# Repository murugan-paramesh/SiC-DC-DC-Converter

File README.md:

# SiC isolated DC-DC converters: PSFB 3 kW baseline and 6.6 kW bidirectional DAB research platform

Two complete, script-generated KiCad 7 hardware designs with their calculations, simulations, firmware
and documentation. Nothing here has been built or measured; every result is labelled by how it was
obtained (calculation, simulation, software-in-the-loop, DRC).

| Design | Where | Status |
|---|---|---|
| **PSFB 3 kW**, 400 V -> 48 V, SiC primary, synchronous rectification, UCC28951 | `hardware/kicad/SiC_PSFB_3kW.kicad_pro`, `docs/`, `tools/`, `simulation/` | schematic generated and netlist-verified; 4-layer PCB generated, fully routed, KiCad DRC 0 errors / 0 unconnected (`hardware/kicad/drc_summary.json`); gerbers/drill/pos in `hardware/outputs/`; switched simulation agrees with the design |
| **DAB 6.6 kW**, 650-850 V <-> 300-450 V bidirectional, SiC both bridges, C2000 control | `SiC_6k6_Industrial_DAB/` (see its README) | full research/engineering chain: requirements, models, design, simulation (Python + ngspice), control + firmware (SIL-tested), 6-layer KiCad PCB, thermal/EMI/safety/FMEA, optimisation, BOM, manufacturing outputs, verification report, research report, lab plan |

Shared tooling: `tools/kicad/` (symbol/footprint generators, hierarchical schematic generator,
`boardgen.py` PCB builder on the pcbnew API with a negotiated-congestion grid router and DRC).

Quick start (PSFB): `python3 tools/psfb_design.py && python3 -m tools.kicad.gen_schematic && python3 -m tools.kicad.gen_pcb`.
Quick start (DAB): see `SiC_6k6_Industrial_DAB/README.md`.

2026 research upgrade: `Advanced_Research_2026/` (gap analysis, verified literature database, digital twin,
adaptive MPC, FEM-lite magnetics, parasitic extraction, robust optimisation, UQ, health monitoring, gate drive,
reliability, HIL plan, cybersecurity, benchmarks, publication drafts, maturity matrix - every module states
its maturity level and what it could not verify; nothing is above L3). Beginner-to-expert learning notes with
viva questions and the combined textbook: `21_Human_Friendly_Learning_Notes/`.

Safety: both designs carry hazardous voltages (420 V / 850 V DC). No prototype should be energised
before an independent engineering review and an approved laboratory procedure
(`SiC_6k6_Industrial_DAB/20_Experimental_Test_Plan/`).

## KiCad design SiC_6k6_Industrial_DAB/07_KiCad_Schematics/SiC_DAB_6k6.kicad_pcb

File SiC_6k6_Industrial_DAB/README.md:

# SiC 6.6 kW Industrial Bidirectional DAB - research and engineering package

Bidirectional dual active bridge, 650-850 V DC <-> 300-450 V DC, 6.6 kW, 100 kHz, 1200 V SiC on
both bridges, TI C2000 digital control. Everything in this directory is generated or verified by
scripts; **no hardware has been built, energised or measured**. The PSFB 3 kW design at the
repository root is the preserved baseline (`Legacy_PSFB_Baseline/README.md`).

## Directory map

| Folder | Content | How it was verified |
|---|---|---|
| `00_Requirements/` | existing-project audit, requirements with explicit service conditions, operating-envelope definition, RTM (`03_RTM.csv`) | reviewed; status column refreshed by `18_Verification/run_verification.py` |
| `01_Literature_Review/` | 38 references (DAB, modulation, SiC, magnetics, control, standards) with a citation-policy note | recalled, to cross-check |
| `02_Topology_Comparison/` | `topology_comparison.py` -> quantitative PSFB/DAB/CLLLC/2-ph/3-ph comparison, decision | script run |
| `03_Mathematical_Models/` | derivations (SPS/EPS/DPS/TPS, ZVS, losses, averaged model) ; code in `dabtools/dab/` | numeric vs closed form < 0.1 % |
| `04_Design_Calculations/` | `dab_design.py` -> `design_values.json`, `design_report.md`, derating/ZVS maps, loss budget, DC link, protection thresholds | script run |
| `05_Simulation/` | closed-loop switched model (`run_switched_sim.py`), ngspice switching model (`gen_spice.py`), results + plots | both run; agree with analysis |
| `06_Magnetics/` | transformer/inductor design, core comparison, insulation, test procedure | script run |
| `07_KiCad_Schematics/` | **KiCad 7 project** `SiC_DAB_6k6.kicad_pro` (5 sheets, 261 components) + the 6-layer PCB `SiC_DAB_6k6.kicad_pcb`, libraries, DRC report | netlist export = design database; DRC via pcbnew: **0 errors, 0 unconnected** (run 27, see 08 and 18) |
| `08_KiCad_PCB/` | layout description, run history, board images (the PCB file lives with the project in 07) | DRC 0 errors / 0 unconnected, 63 silkscreen/stub warnings |
| `09_Component_Libraries/` | pointer to `07_KiCad_Schematics/lib/` and the generators | pin-existence check |
| `10_Firmware/` | portable C control core, protocol, C2000 HAL (not compiled), SIL harness (`make test`) | 30 SIL checks pass (gcc) |
| `11_Control_Algorithms/` | loop design, modulation comparison, MPC alternative, `control_params.json` | script run |
| `12_Optimization/` | exhaustive design-space exploration, Pareto front, sensitivities | script run |
| `13_Thermal_Analysis/` | losses -> Tj, cooling options, derating | script run |
| `14_EMI_EMC/` | DM/CM estimate, filter, standards, pre-compliance plan | script run |
| `15_Safety_Reliability/` | insulation coordination (IEC 62477-1/60664-1 basis), protection coordination, FMEA | analysis |
| `16_BOM/` | BOM with ratings/derating, flags for unverified parts, off-board items | generated |
| `17_Manufacturing/` | stack-up, notes, `export_outputs.py` (gerbers, drill, pos, PDFs) | kicad-cli |
| `18_Verification/` | `run_verification.py` -> `verification_report.md` (what ran, what passed) | - |
| `19_Research_Report/` | `build_report.py` -> `report.md` (28 chapters, numbers pulled from result files) | generated |
| `20_Experimental_Test_Plan/` | staged laboratory plan, instruments, criteria, safety controls | procedure only |
| `dabtools/` | Python packages: `dab/` (models), `kicad_dab/` (design database, schematic/PCB/BOM generators) | - |

## Reproduce everything

```
cd SiC_6k6_Industrial_DAB
pip install numpy matplotlib            # KiCad 7 (kicad-cli + pcbnew python), ngspice, gcc required
python3 02_Topology_Comparison/topology_comparison.py
python3 04_Design_Calculations/dab_design.py
python3 06_Magnetics/transformer_design.py
python3 05_Simulation/run_switched_sim.py && python3 05_Simulation/gen_spice.py
python3 11_Control_Algorithms/control_design.py
python3 12_Optimization/optimize.py
python3 13_Thermal_Analysis/thermal_analysis.py && python3 14_EMI_EMC/emi_analysis.py
(cd 10_Firmware && python3 tools/gen_params.py && make test)
python3 dabtools/kicad_dab/gen_sch_dab.py        # schematic + libraries + netlist check
python3 dabtools/kicad_dab/gen_pcb_dab.py        # placement, planes, routing, zone fill, DRC (long)
python3 dabtools/kicad_dab/bom_dab.py
python3 17_Manufacturing/export_outputs.py
python3 18_Verification/run_verification.py
python3 19_Research_Report/build_report.py
```

## Completion matrix

See `18_Verification/verification_report.md` for the current tool results and
`00_Requirements/03_RTM.csv` for the per-requirement status. Summary of the states used:
*completed* (artefact exists and its generator ran), *generated but not verified* (C2000 HAL,
BoosterPack mapping, bias-module choice), *simulation-validated* (control, power stage),
*engineering-reviewed* (none yet - independent review required), *experimentally validated*
(none), *blocked* (push to GitHub pending repository access), *remaining work* (chapter 23 of
the report).

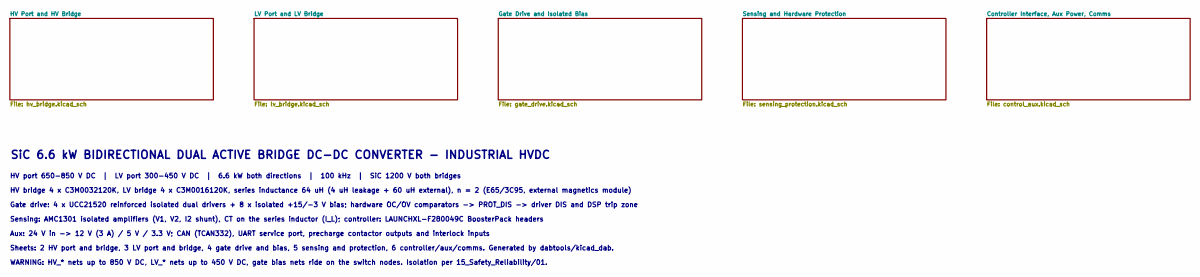
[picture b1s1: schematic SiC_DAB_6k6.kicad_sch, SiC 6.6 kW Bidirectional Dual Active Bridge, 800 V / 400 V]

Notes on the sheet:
SiC 6.6 kW BIDIRECTIONAL DUAL ACTIVE BRIDGE DC-DC CONVERTER - INDUSTRIAL HVDC
HV port 650-850 V DC | LV port 300-450 V DC | 6.6 kW both directions | 100 kHz | SiC 1200 V both bridges
HV bridge 4 x C3M0032120K, LV bridge 4 x C3M0016120K, series inductance 64 uH (4 uH leakage + 60 uH external), n = 2 (E65/3C95, external magnetics module)
Gate drive: 4 x UCC21520 reinforced isolated dual drivers + 8 x isolated +15/-3 V bias; hardware OC/OV comparators -> PROT_DIS -> driver DIS and DSP trip zone
Sensing: AMC1301 isolated amplifiers (V1, V2, I2 shunt), CT on the series inductor (I_L); controller: LAUNCHXL-F280049C BoosterPack headers
Aux: 24 V in -> 12 V (3 A) / 5 V / 3.3 V; CAN (TCAN332), UART service port, precharge contactor outputs and interlock inputs
Sheets: 2 HV port and bridge, 3 LV port and bridge, 4 gate drive and bias, 5 sensing and protection, 6 controller/aux/comms. Generated by dabtools/kicad_dab.
WARNING: HV_* nets up to 850 V DC, LV_* nets up to 450 V DC, gate bias nets ride on the switch nodes. Isolation per 15_Safety_Reliability/01.

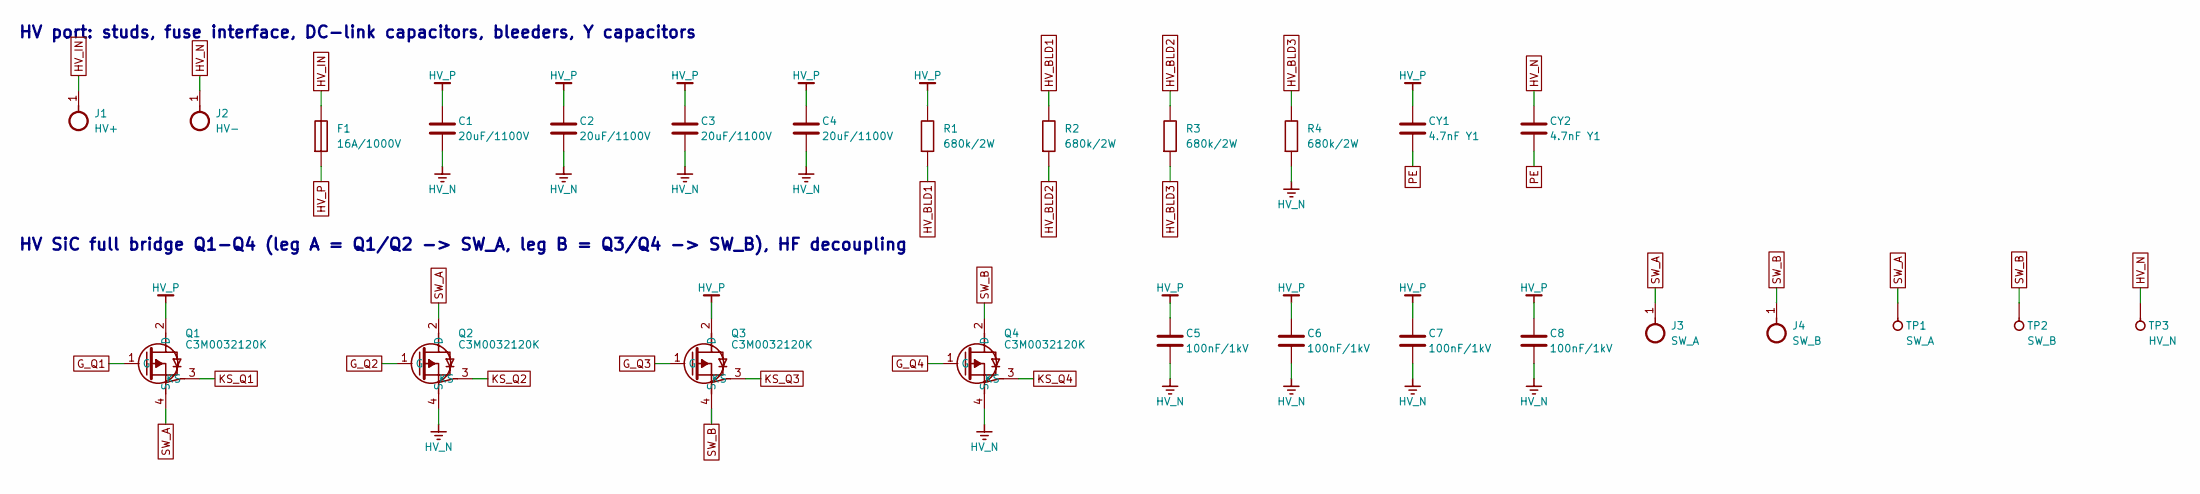
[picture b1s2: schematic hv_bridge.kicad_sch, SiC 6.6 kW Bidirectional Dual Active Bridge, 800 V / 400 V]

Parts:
C1, C2, C3, C4: 20uF/1100V; C_Film_P52.5; MPN TDK B32778J0206K (verify 1100 V variant)
C5, C6, C7, C8: 100nF/1kV; C_2220; MPN TDK CGA9N4X7T2W104K (verify)
CY1, CY2: 4.7nF Y1; C_Y1_P12.5; MPN Vishay VY1472M63Y5UQ63V0
F1: 16A/1000V; Fuse_Terminal_M6; MPN Bussmann FWP-16A14F class (verify)
J1: HV+; Stud_M6
J2: HV-; Stud_M6
J3: SW_A; Stud_M6
J4: SW_B; Stud_M6
Q1, Q2, Q3, Q4: C3M0032120K; TO-247-4_Vertical; MPN Wolfspeed C3M0032120K
R1, R2, R3, R4: 680k/2W; R_2512
TP1: SW_A; TestPoint
TP2: SW_B; TestPoint
TP3: HV_N; TestPoint

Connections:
G_Q1: Q1.1 (G); also elsewhere on the board
G_Q2: Q2.1 (G); also elsewhere on the board
G_Q3: Q3.1 (G); also elsewhere on the board
G_Q4: Q4.1 (G); also elsewhere on the board
HV_BLD1: R1.2, R2.1
HV_BLD2: R2.2, R3.1
HV_BLD3: R3.2, R4.1
HV_IN: F1.1, J1.1
HV_N: C1.2, C2.2, C3.2, C4.2, C5.2, C6.2, C7.2, C8.2, CY2.1, J2.1, Q2.4 (S), Q4.4 (S), R4.2, TP3.1; also elsewhere on the board
HV_P: C1.1, C2.1, C3.1, C4.1, C5.1, C6.1, C7.1, C8.1, CY1.1, F1.2, Q1.2 (D), Q3.2 (D), R1.1; also elsewhere on the board
KS_Q1: Q1.3 (KS); also elsewhere on the board
KS_Q2: Q2.3 (KS); also elsewhere on the board
KS_Q3: Q3.3 (KS); also elsewhere on the board
KS_Q4: Q4.3 (KS); also elsewhere on the board
PE_HV: CY1.2, CY2.2; also elsewhere on the board
SW_A: J3.1, Q1.4 (S), Q2.2 (D), TP1.1; also elsewhere on the board
SW_B: J4.1, Q3.4 (S), Q4.2 (D), TP2.1

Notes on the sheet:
HV port: studs, fuse interface, DC-link capacitors, bleeders, Y capacitors
HV SiC full bridge Q1-Q4 (leg A = Q1/Q2 -> SW_A, leg B = Q3/Q4 -> SW_B), HF decoupling

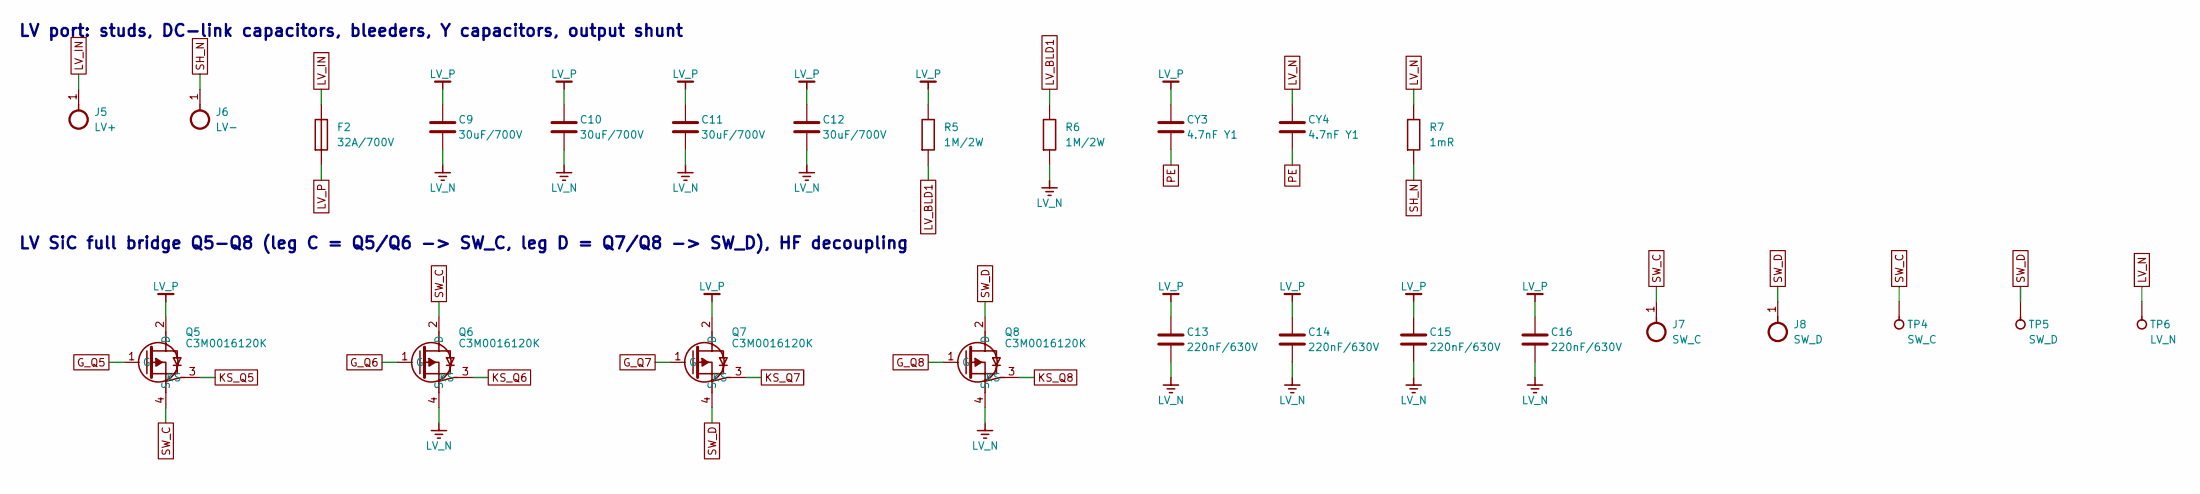
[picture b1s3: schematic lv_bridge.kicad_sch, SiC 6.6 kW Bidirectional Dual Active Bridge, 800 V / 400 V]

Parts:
C9, C10, C11, C12: 30uF/700V; C_Film_P37.5; MPN TDK B32778G7306K (verify)
C13, C14, C15, C16: 220nF/630V; C_2220; MPN TDK CGA9P4X7T2J224K (verify)
CY3, CY4: 4.7nF Y1; C_Y1_P12.5; MPN Vishay VY1472M63Y5UQ63V0
F2: 32A/700V; Fuse_Terminal_M6; MPN Bussmann FWP-32A14F class (verify)
J5: LV+; Stud_M6
J6: LV-; Stud_M6
J7: SW_C; Stud_M6
J8: SW_D; Stud_M6
Q5, Q6, Q7, Q8: C3M0016120K; TO-247-4_Vertical; MPN Wolfspeed C3M0016120K
R5, R6: 1M/2W; R_2512
R7: 1mR; R_Shunt_8518; MPN Vishay WSBS8518L1000JK
TP4: SW_C; TestPoint
TP5: SW_D; TestPoint
TP6: LV_N; TestPoint

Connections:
G_Q5: Q5.1 (G); also elsewhere on the board
G_Q6: Q6.1 (G); also elsewhere on the board
G_Q7: Q7.1 (G); also elsewhere on the board
G_Q8: Q8.1 (G); also elsewhere on the board
KS_Q5: Q5.3 (KS); also elsewhere on the board
KS_Q6: Q6.3 (KS); also elsewhere on the board
KS_Q7: Q7.3 (KS); also elsewhere on the board
KS_Q8: Q8.3 (KS); also elsewhere on the board
LV_BLD1: R5.2, R6.1
LV_IN: F2.1, J5.1
LV_N: C9.2, C10.2, C11.2, C12.2, C13.2, C14.2, C15.2, C16.2, CY4.1, Q6.4 (S), Q8.4 (S), R6.2, R7.1, TP6.1; also elsewhere on the board
LV_P: C9.1, C10.1, C11.1, C12.1, C13.1, C14.1, C15.1, C16.1, CY3.1, F2.2, Q5.2 (D), Q7.2 (D), R5.1; also elsewhere on the board
PE_LV: CY3.2, CY4.2; also elsewhere on the board
SH_N: J6.1, R7.2; also elsewhere on the board
SW_C: J7.1, Q5.4 (S), Q6.2 (D), TP4.1
SW_D: J8.1, Q7.4 (S), Q8.2 (D), TP5.1

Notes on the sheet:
LV port: studs, DC-link capacitors, bleeders, Y capacitors, output shunt
LV SiC full bridge Q5-Q8 (leg C = Q5/Q6 -> SW_C, leg D = Q7/Q8 -> SW_D), HF decoupling

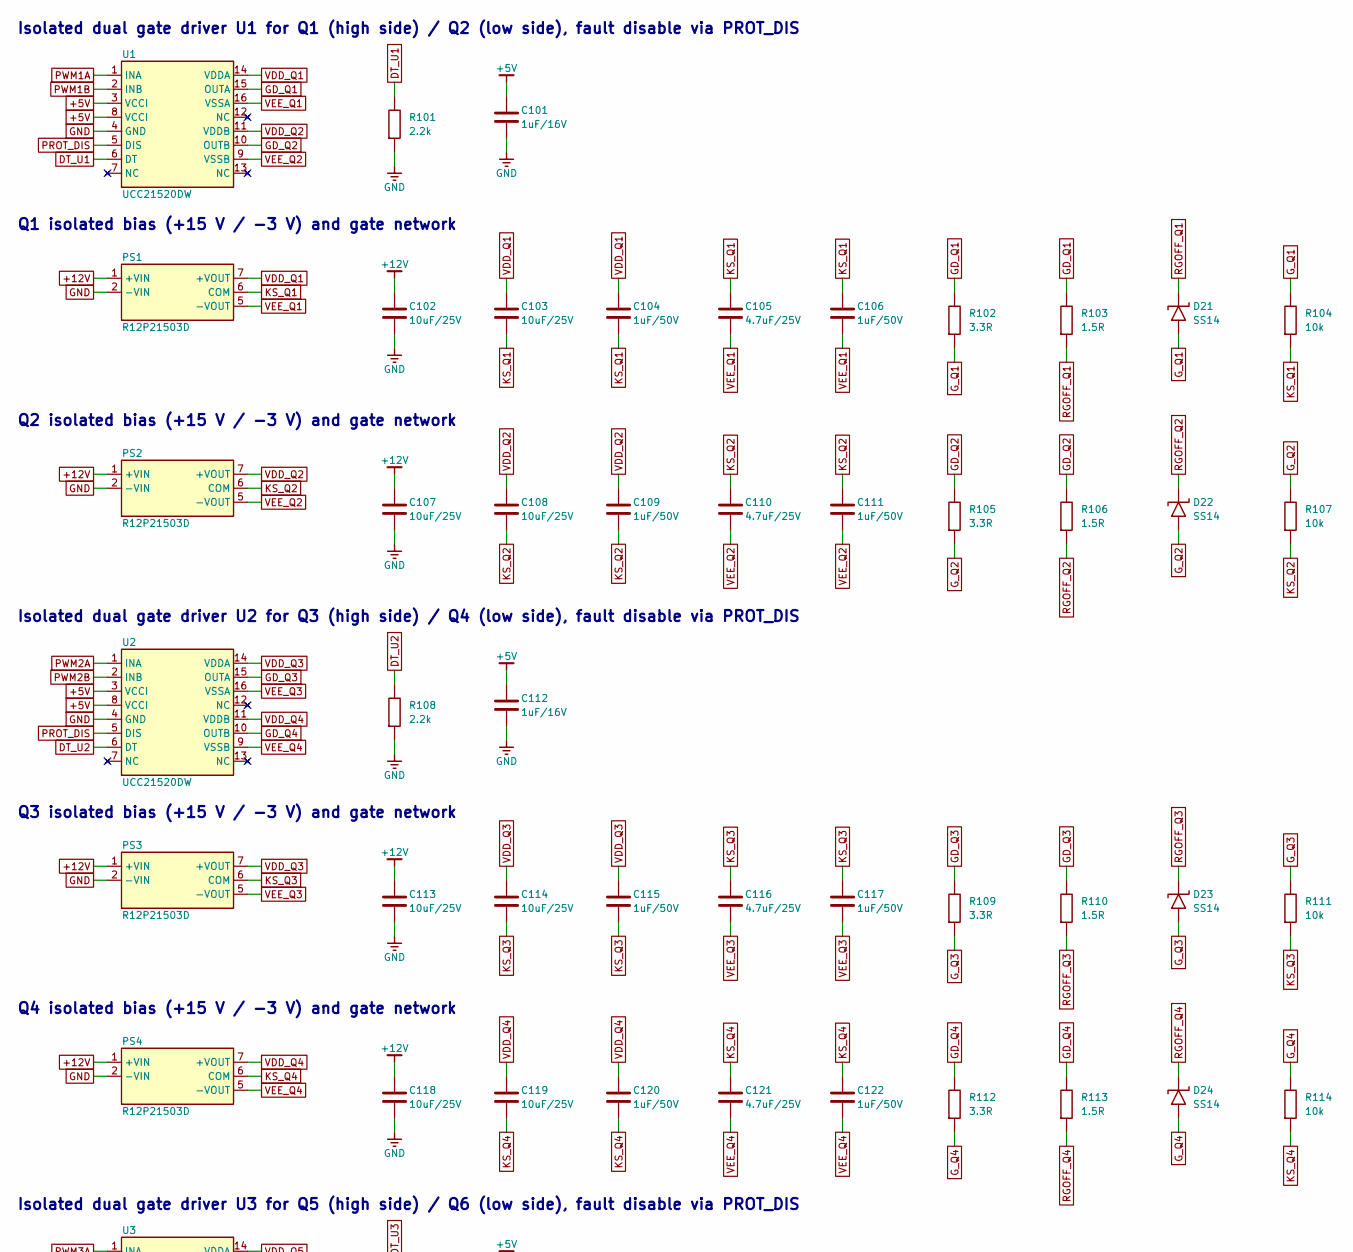
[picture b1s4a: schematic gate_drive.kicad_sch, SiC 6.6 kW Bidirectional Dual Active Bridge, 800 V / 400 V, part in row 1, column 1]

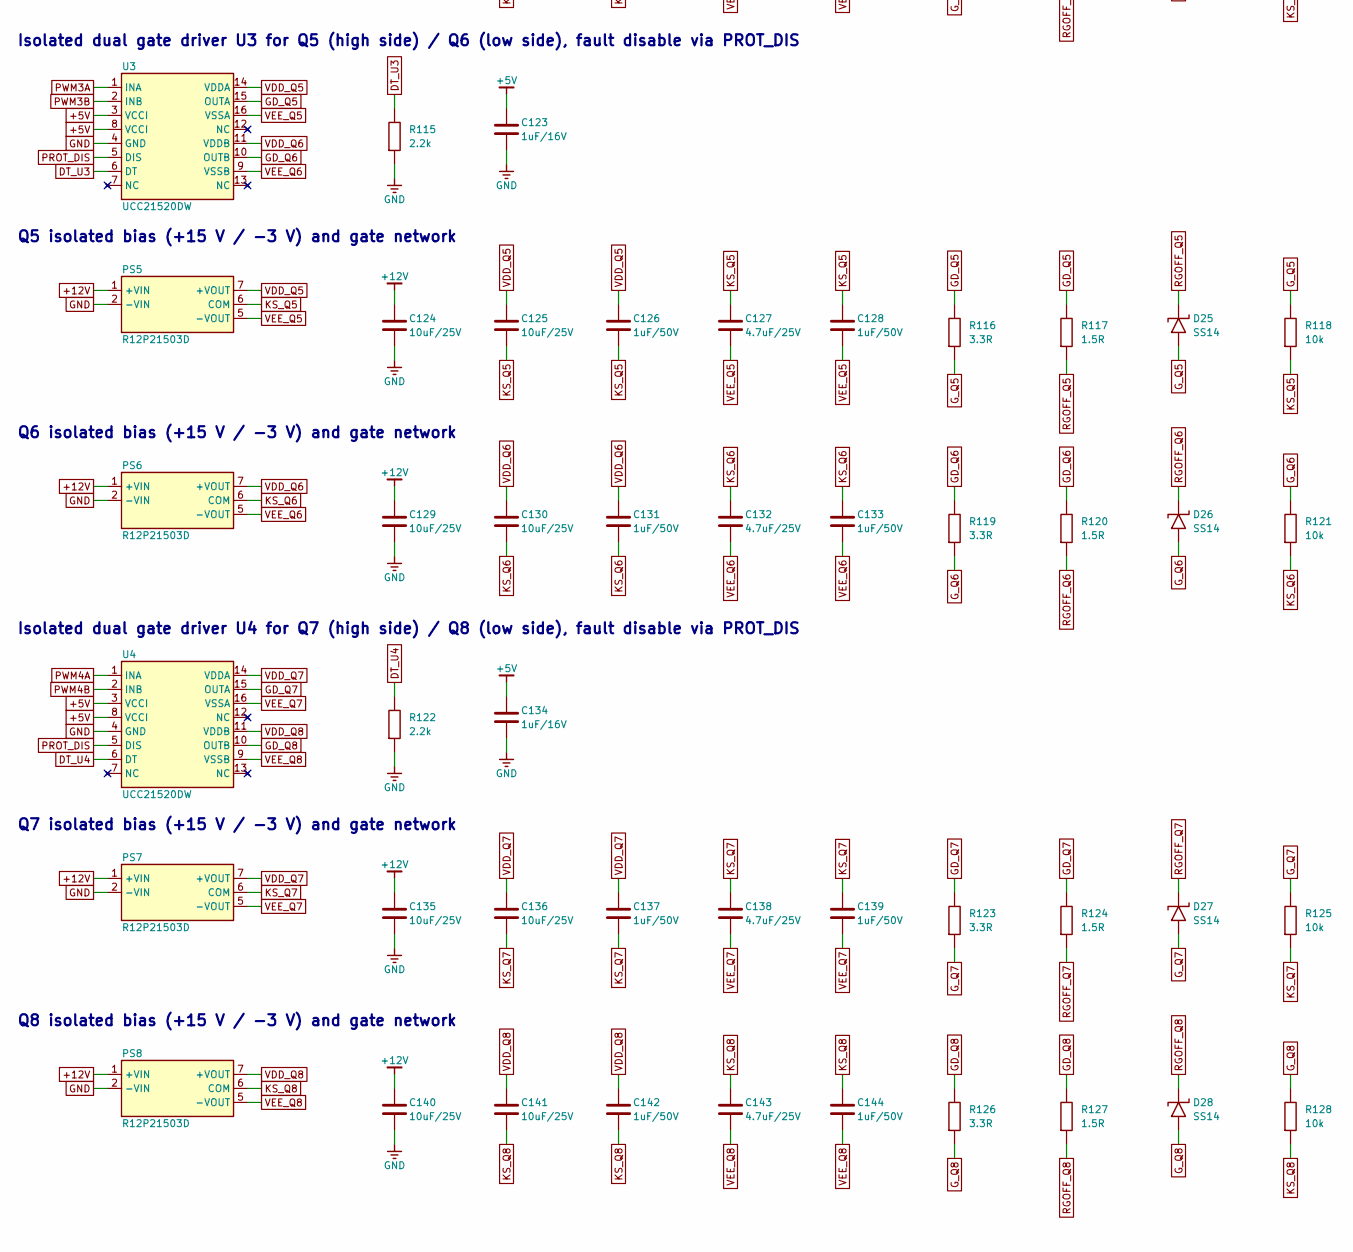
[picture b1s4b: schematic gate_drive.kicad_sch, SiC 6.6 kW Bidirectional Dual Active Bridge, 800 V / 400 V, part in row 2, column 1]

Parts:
C101, C112, C123, C134: 1uF/16V; C_0603
C102, C103, C107, C108, C113, C114, C118, C119, C124, C125, C129, C130, C135, C136, C140, C141: 10uF/25V; C_1206
C104, C106, C109, C111, C115, C117, C120, C122, C126, C128, C131, C133, C137, C139, C142, C144: 1uF/50V; C_0603
C105, C110, C116, C121, C127, C132, C138, C143: 4.7uF/25V; C_0805
D21, D22, D23, D24, D25, D26, D27, D28: SS14; D_SMA; MPN Vishay SS14
PS1, PS2, PS3, PS4, PS5, PS6, PS7, PS8: R12P21503D; SIP-7_IsoDCDC; MPN RECOM R12P21503D (basic-class isolation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
R101, R108, R115, R122: 2.2k; R_0603
R102, R105, R109, R112, R116, R119, R123, R126: 3.3R; R_1206
R103, R106, R110, R113, R117, R120, R124, R127: 1.5R; R_1206
R104, R107, R111, R114, R118, R121, R125, R128: 10k; R_0603
U1, U2, U3, U4: UCC21520DW; SOIC-16W; MPN TI UCC21520DW

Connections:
+5V: C101.1, C112.1, C123.1, C134.1, U1.3 (VCCI), U1.8 (VCCI), U2.3 (VCCI), U2.8 (VCCI), U3.3 (VCCI), U3.8 (VCCI), U4.3 (VCCI), U4.8 (VCCI); also elsewhere on the board
+12V: C102.1, C107.1, C113.1, C118.1, C124.1, C129.1, C135.1, C140.1, PS1.1 (+VIN), PS2.1 (+VIN), PS3.1 (+VIN), PS4.1 (+VIN), PS5.1 (+VIN), PS6.1 (+VIN), PS7.1 (+VIN), PS8.1 (+VIN); also elsewhere on the board
DT_U1: R101.1, U1.6 (DT)
DT_U2: R108.1, U2.6 (DT)
DT_U3: R115.1, U3.6 (DT)
DT_U4: R122.1, U4.6 (DT)
GD_Q1: R102.1, R103.1, U1.15 (OUTA)
GD_Q2: R105.1, R106.1, U1.10 (OUTB)
GD_Q3: R109.1, R110.1, U2.15 (OUTA)
GD_Q4: R112.1, R113.1, U2.10 (OUTB)
GD_Q5: R116.1, R117.1, U3.15 (OUTA)
GD_Q6: R119.1, R120.1, U3.10 (OUTB)
GD_Q7: R123.1, R124.1, U4.15 (OUTA)
GD_Q8: R126.1, R127.1, U4.10 (OUTB)
GND: C101.2, C102.2, C107.2, C112.2, C113.2, C118.2, C123.2, C124.2, C129.2, C134.2, C135.2, C140.2, PS1.2 (-VIN), PS2.2 (-VIN), PS3.2 (-VIN), PS4.2 (-VIN), PS5.2 (-VIN), PS6.2 (-VIN), PS7.2 (-VIN), PS8.2 (-VIN), R101.2, R108.2, R115.2, R122.2, U1.4 (GND), U2.4 (GND), U3.4 (GND), U4.4 (GND); also elsewhere on the board
G_Q1: D21.2 (A), R102.2, R104.1; also elsewhere on the board
G_Q2: D22.2 (A), R105.2, R107.1; also elsewhere on the board
G_Q3: D23.2 (A), R109.2, R111.1; also elsewhere on the board
G_Q4: D24.2 (A), R112.2, R114.1; also elsewhere on the board
G_Q5: D25.2 (A), R116.2, R118.1; also elsewhere on the board
G_Q6: D26.2 (A), R119.2, R121.1; also elsewhere on the board
G_Q7: D27.2 (A), R123.2, R125.1; also elsewhere on the board
G_Q8: D28.2 (A), R126.2, R128.1; also elsewhere on the board
KS_Q1: C103.2, C104.2, C105.1, C106.1, PS1.6 (COM), R104.2; also elsewhere on the board
KS_Q2: C108.2, C109.2, C110.1, C111.1, PS2.6 (COM), R107.2; also elsewhere on the board
KS_Q3: C114.2, C115.2, C116.1, C117.1, PS3.6 (COM), R111.2; also elsewhere on the board
KS_Q4: C119.2, C120.2, C121.1, C122.1, PS4.6 (COM), R114.2; also elsewhere on the board
KS_Q5: C125.2, C126.2, C127.1, C128.1, PS5.6 (COM), R118.2; also elsewhere on the board
KS_Q6: C130.2, C131.2, C132.1, C133.1, PS6.6 (COM), R121.2; also elsewhere on the board
KS_Q7: C136.2, C137.2, C138.1, C139.1, PS7.6 (COM), R125.2; also elsewhere on the board
KS_Q8: C141.2, C142.2, C143.1, C144.1, PS8.6 (COM), R128.2; also elsewhere on the board
PROT_DIS: U1.5 (DIS), U2.5 (DIS), U3.5 (DIS), U4.5 (DIS); also elsewhere on the board
PWM1A: U1.1 (INA); also elsewhere on the board
PWM1B: U1.2 (INB); also elsewhere on the board
PWM2A: U2.1 (INA); also elsewhere on the board
PWM2B: U2.2 (INB); also elsewhere on the board
PWM3A: U3.1 (INA); also elsewhere on the board
PWM3B: U3.2 (INB); also elsewhere on the board
PWM4A: U4.1 (INA); also elsewhere on the board
PWM4B: U4.2 (INB); also elsewhere on the board
RGOFF_Q1: D21.1 (K), R103.2
RGOFF_Q2: D22.1 (K), R106.2
RGOFF_Q3: D23.1 (K), R110.2
RGOFF_Q4: D24.1 (K), R113.2
RGOFF_Q5: D25.1 (K), R117.2
RGOFF_Q6: D26.1 (K), R120.2
RGOFF_Q7: D27.1 (K), R124.2
RGOFF_Q8: D28.1 (K), R127.2
VDD_Q1: C103.1, C104.1, PS1.7 (+VOUT), U1.14 (VDDA)
VDD_Q2: C108.1, C109.1, PS2.7 (+VOUT), U1.11 (VDDB)
VDD_Q3: C114.1, C115.1, PS3.7 (+VOUT), U2.14 (VDDA)
VDD_Q4: C119.1, C120.1, PS4.7 (+VOUT), U2.11 (VDDB)
VDD_Q5: C125.1, C126.1, PS5.7 (+VOUT), U3.14 (VDDA)
VDD_Q6: C130.1, C131.1, PS6.7 (+VOUT), U3.11 (VDDB)
VDD_Q7: C136.1, C137.1, PS7.7 (+VOUT), U4.14 (VDDA)
VDD_Q8: C141.1, C142.1, PS8.7 (+VOUT), U4.11 (VDDB)
VEE_Q1: C105.2, C106.2, PS1.5 (-VOUT), U1.16 (VSSA)
VEE_Q2: C110.2, C111.2, PS2.5 (-VOUT), U1.9 (VSSB)
VEE_Q3: C116.2, C117.2, PS3.5 (-VOUT), U2.16 (VSSA)
VEE_Q4: C121.2, C122.2, PS4.5 (-VOUT), U2.9 (VSSB)
VEE_Q5: C127.2, C128.2, PS5.5 (-VOUT), U3.16 (VSSA)
VEE_Q6: C132.2, C133.2, PS6.5 (-VOUT), U3.9 (VSSB)
VEE_Q7: C138.2, C139.2, PS7.5 (-VOUT), U4.16 (VSSA)
VEE_Q8: C143.2, C144.2, PS8.5 (-VOUT), U4.9 (VSSB)

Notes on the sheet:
Isolated dual gate driver U1 for Q1 (high side) / Q2 (low side), fault disable via PROT_DIS
Q1 isolated bias (+15 V / -3 V) and gate network
Q2 isolated bias (+15 V / -3 V) and gate network
Isolated dual gate driver U2 for Q3 (high side) / Q4 (low side), fault disable via PROT_DIS
Q3 isolated bias (+15 V / -3 V) and gate network
Q4 isolated bias (+15 V / -3 V) and gate network
Isolated dual gate driver U3 for Q5 (high side) / Q6 (low side), fault disable via PROT_DIS
Q5 isolated bias (+15 V / -3 V) and gate network
Q6 isolated bias (+15 V / -3 V) and gate network
Isolated dual gate driver U4 for Q7 (high side) / Q8 (low side), fault disable via PROT_DIS
Q7 isolated bias (+15 V / -3 V) and gate network
Q8 isolated bias (+15 V / -3 V) and gate network

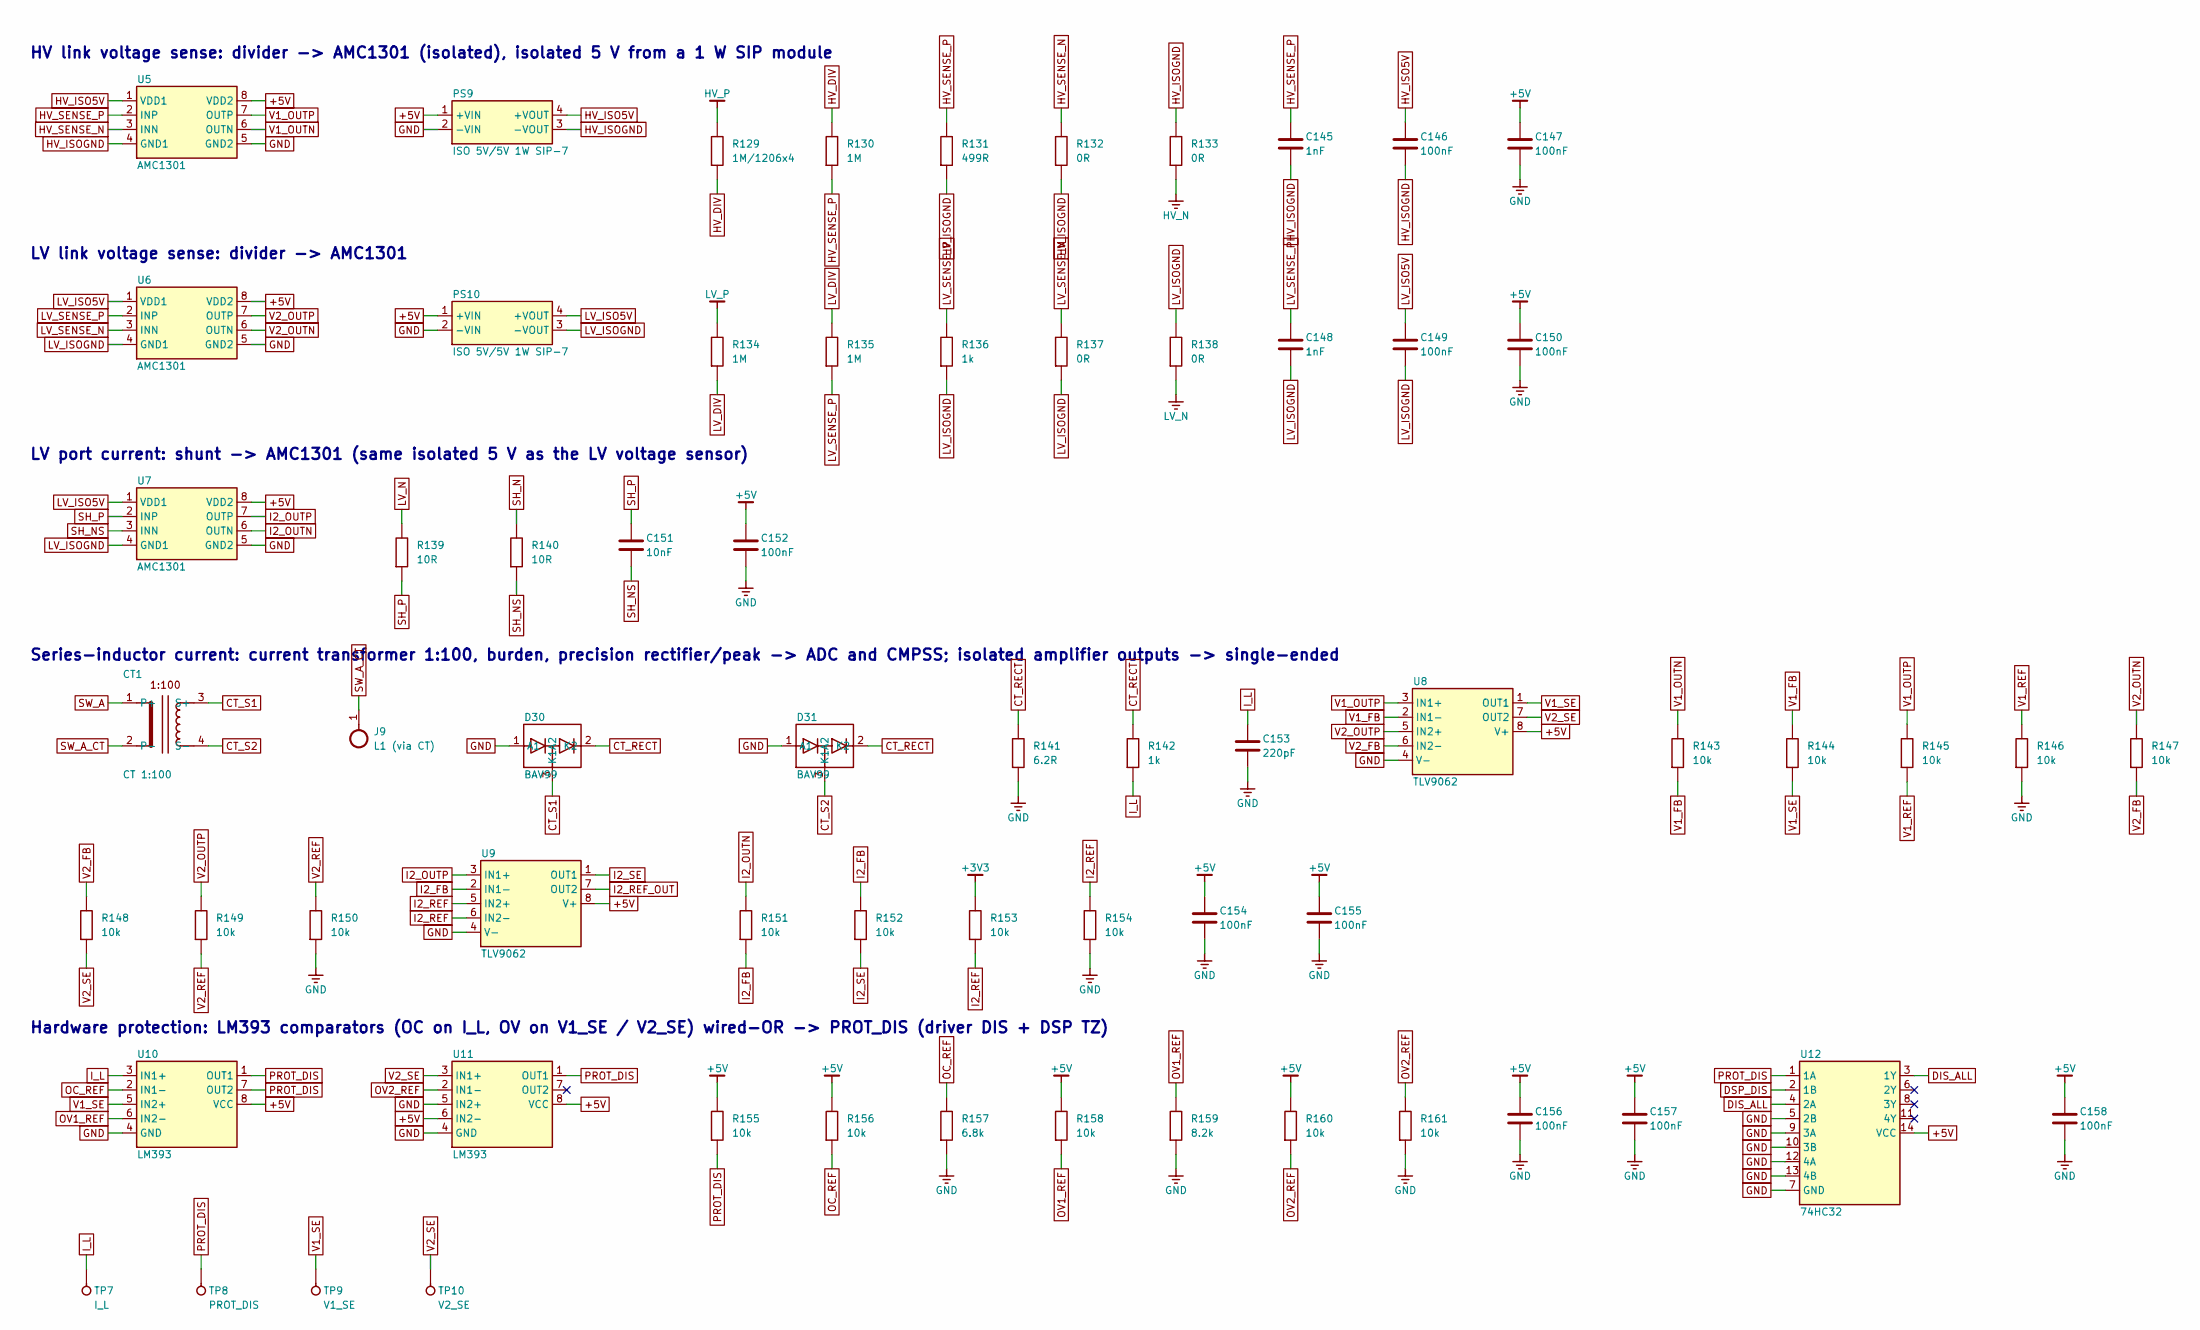
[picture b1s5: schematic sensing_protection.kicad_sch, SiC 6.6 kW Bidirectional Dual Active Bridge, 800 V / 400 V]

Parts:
C145, C148: 1nF; C_0603
C146, C147, C149, C150, C152, C154, C155, C156, C157, C158: 100nF; C_0603
C151: 10nF; C_0603
C153: 220pF; C_0603
CT1: CT 1:100; CT_Toroid_Straddle; MPN Magnetics ZW42908TC + 100T AWG32
D30, D31: BAV99; SOT-23
J9: L1 (via CT); Stud_M6
PS9: ISO 5V/5V 1W SIP-7; SIP-7_IsoDCDC_1W; MPN TBD - 1 W 5 V->5 V isolated module, SIP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
PS10: ISO 5V/5V 1W SIP-7; SIP-7_IsoDCDC_1W; MPN TBD - as PS9
R129: 1M/1206x4; R_1206
R130, R134, R135: 1M; R_1206
R131: 499R; R_0603
R132, R137: 0R; R_0603
R133, R138: 0R; R_0805
R136, R142: 1k; R_0603
R139, R140: 10R; R_0603
R141: 6.2R; R_0805
R143, R144, R145, R146, R147, R148, R149, R150, R151, R152, R153, R154, R155, R156, R158, R160, R161: 10k; R_0603
R157: 6.8k; R_0603
R159: 8.2k; R_0603
TP7: I_L; TestPoint
TP8: PROT_DIS; TestPoint
TP9: V1_SE; TestPoint
TP10: V2_SE; TestPoint
U5, U6, U7: AMC1301; SOIC-8W; MPN TI AMC1301DWV
U8, U9: TLV9062; SOIC-8; MPN TI TLV9062IDR
U10, U11: LM393; SOIC-8; MPN TI LM393DR
U12: 74HC32; SOIC-14; MPN TI SN74HC32D

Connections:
+3V3: R153.1; also elsewhere on the board
+5V: C147.1, C150.1, C152.1, C154.1, C155.1, C156.1, C157.1, C158.1, PS9.1 (+VIN), PS10.1 (+VIN), R155.1, R156.1, R158.1, R160.1, U5.8 (VDD2), U6.8 (VDD2), U7.8 (VDD2), U8.8 (V+), U9.8 (V+), U10.8 (VCC), U11.6 (IN2-), U11.8 (VCC), U12.14 (VCC); also elsewhere on the board
CT_RECT: D30.2 (K2), D31.2 (K2), R141.1, R142.1
CT_S1: CT1.3 (S+), D30.3 (K1A2)
CT_S2: CT1.4 (S-), D31.3 (K1A2)
DIS_ALL: U12.3 (1Y), U12.4 (2A)
DSP_DIS: U12.2 (1B); also elsewhere on the board
GND: C147.2, C150.2, C152.2, C153.2, C154.2, C155.2, C156.2, C157.2, C158.2, D30.1 (A1), D31.1 (A1), PS9.2 (-VIN), PS10.2 (-VIN), R141.2, R146.2, R150.2, R154.2, R157.2, R159.2, R161.2, U5.5 (GND2), U6.5 (GND2), U7.5 (GND2), U8.4 (V-), U9.4 (V-), U10.4 (GND), U11.4 (GND), U11.5 (IN2+), U12.5 (2B), U12.7 (GND), U12.9 (3A), U12.10 (3B), U12.12 (4A), U12.13 (4B); also elsewhere on the board
HV_DIV: R129.2, R130.1
HV_ISO5V: C146.1, PS9.4 (+VOUT), U5.1 (VDD1)
HV_ISOGND: C145.2, C146.2, PS9.3 (-VOUT), R131.2, R132.2, R133.1, U5.4 (GND1)
HV_N: R133.2; also elsewhere on the board
HV_P: R129.1; also elsewhere on the board
HV_SENSE_N: R132.1, U5.3 (INN)
HV_SENSE_P: C145.1, R130.2, R131.1, U5.2 (INP)
I2_FB: R151.2, R152.1, U9.2 (IN1-)
I2_OUTN: R151.1, U7.6 (OUTN)
I2_OUTP: U7.7 (OUTP), U9.3 (IN1+)
I2_REF: R153.2, R154.1, U9.5 (IN2+), U9.6 (IN2-)
I2_REF_OUT: U9.7 (OUT2)
I2_SE: R152.2, U9.1 (OUT1); also elsewhere on the board
I_L: C153.1, R142.2, TP7.1, U10.3 (IN1+); also elsewhere on the board
LV_DIV: R134.2, R135.1
LV_ISO5V: C149.1, PS10.4 (+VOUT), U6.1 (VDD1), U7.1 (VDD1)
LV_ISOGND: C148.2, C149.2, PS10.3 (-VOUT), R136.2, R137.2, R138.1, U6.4 (GND1), U7.4 (GND1)
LV_N: R138.2, R139.1; also elsewhere on the board
LV_P: R134.1; also elsewhere on the board
LV_SENSE_N: R137.1, U6.3 (INN)
LV_SENSE_P: C148.1, R135.2, R136.1, U6.2 (INP)
OC_REF: R156.2, R157.1, U10.2 (IN1-)
OV1_REF: R158.2, R159.1, U10.6 (IN2-)
OV2_REF: R160.2, R161.1, U11.2 (IN1-)
PROT_DIS: R155.2, TP8.1, U10.1 (OUT1), U10.7 (OUT2), U11.1 (OUT1), U12.1 (1A); also elsewhere on the board
SH_N: R140.1; also elsewhere on the board
SH_NS: C151.2, R140.2, U7.3 (INN)
SH_P: C151.1, R139.2, U7.2 (INP)
SW_A: CT1.1 (P+); also elsewhere on the board
SW_A_CT: CT1.2 (P-), J9.1
V1_FB: R143.2, R144.1, U8.2 (IN1-)
V1_OUTN: R143.1, U5.6 (OUTN)
V1_OUTP: R145.1, U5.7 (OUTP), U8.3 (IN1+)
V1_REF: R145.2, R146.1
V1_SE: R144.2, TP9.1, U8.1 (OUT1), U10.5 (IN2+); also elsewhere on the board
V2_FB: R147.2, R148.1, U8.6 (IN2-)
V2_OUTN: R147.1, U6.6 (OUTN)
V2_OUTP: R149.1, U6.7 (OUTP), U8.5 (IN2+)
V2_REF: R149.2, R150.1
V2_SE: R148.2, TP10.1, U8.7 (OUT2), U11.3 (IN1+); also elsewhere on the board

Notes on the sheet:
HV link voltage sense: divider -> AMC1301 (isolated), isolated 5 V from a 1 W SIP module
LV link voltage sense: divider -> AMC1301
LV port current: shunt -> AMC1301 (same isolated 5 V as the LV voltage sensor)
Series-inductor current: current transformer 1:100, burden, precision rectifier/peak -> ADC and CMPSS; isolated amplifier outputs -> single-ended
Hardware protection: LM393 comparators (OC on I_L, OV on V1_SE / V2_SE) wired-OR -> PROT_DIS (driver DIS + DSP TZ)
